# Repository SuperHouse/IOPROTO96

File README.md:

I/O Breakout To Prototyping Area (96 Point)
===========================================
Copyright 2017 SuperHouse Pty Ltd  
SuperHouse site:  www.superhouse.tv  

Breaks out a 2x6 pin header to a 96-point prototyping area.

Features:

 * 8 data lines
 * GND, VIN, IOREF, and RESET passed through
 * 8x12 grid prototyping area

More information is available at:

  http://www.superhouse.tv/ioproto96

INSTALLATION
------------
The design is saved as an EAGLE project. EAGLE PCB design software is
available from www.cadsoftusa.com free for non-commercial use. To use
this project download it and place the directory containing these files
into the "eagle" directory on your computer. Then open EAGLE and
navigate to the project.

DISTRIBUTION
------------
The specific terms of distribution of this project are governed by the
license referenced below.

LICENSE
-------
Licensed under the TAPR Open Hardware License (www.tapr.org/OHL).
The "license" folder within this repository also contains a copy of
this license in plain text format.

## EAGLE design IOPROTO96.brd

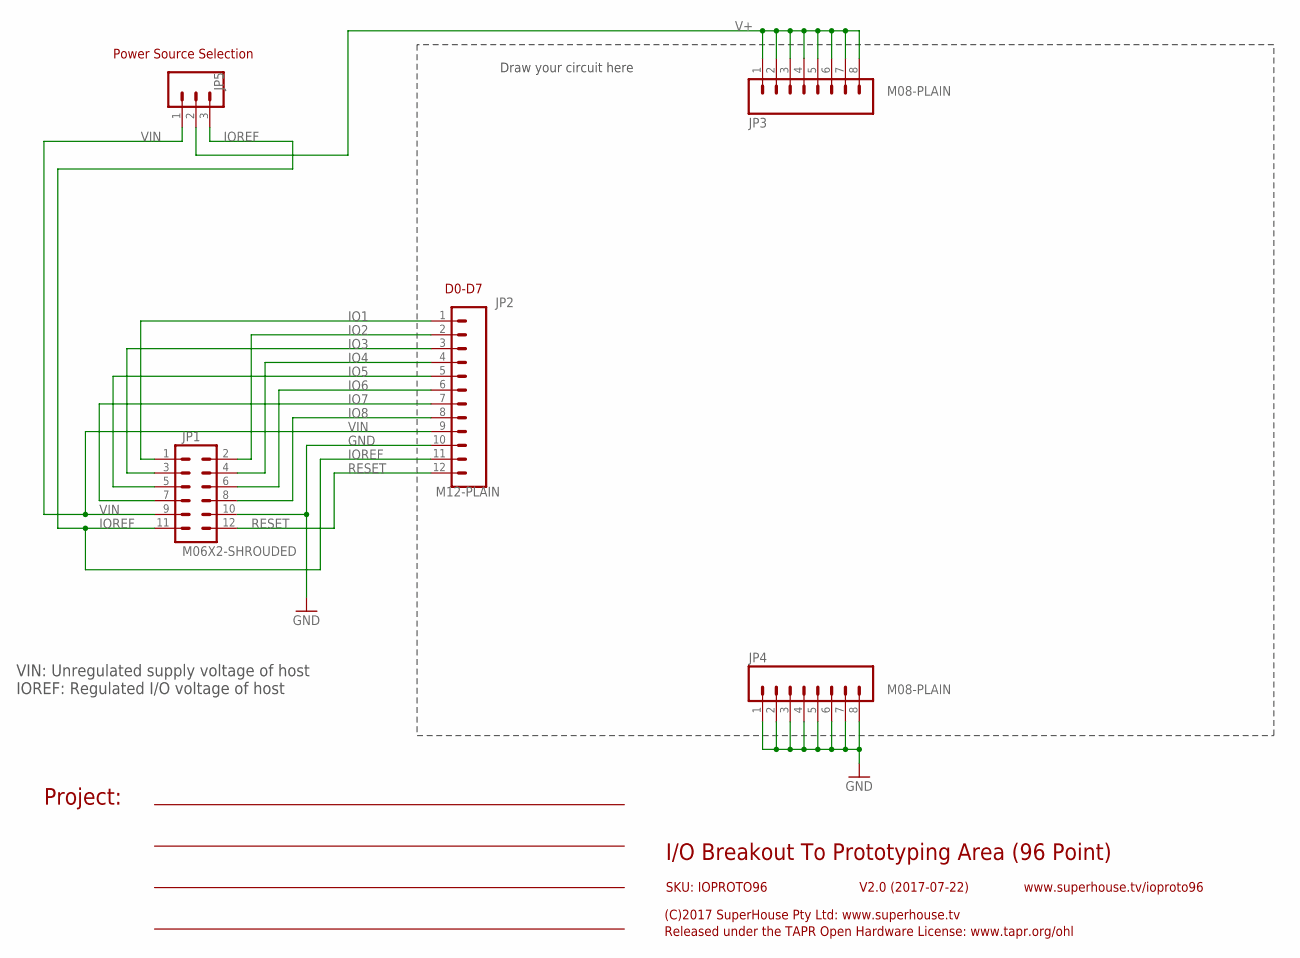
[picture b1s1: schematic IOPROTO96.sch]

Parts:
JP1: M06X2-SHROUDED; 2X6-SHROUDED
JP2: M12-PLAIN; 1X12
JP3, JP4: M08-PLAIN; 1X08
JP5: M03-PIN; 1X03-P

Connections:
GND: JP1.10, JP2.10, JP4.1, JP4.2, JP4.3, JP4.4, JP4.5, JP4.6, JP4.7, JP4.8
IO1: JP1.1, JP2.1
IO2: JP1.2, JP2.2
IO3: JP1.3, JP2.3
IO4: JP1.4, JP2.4
IO5: JP1.5, JP2.5
IO6: JP1.6, JP2.6
IO7: JP1.7, JP2.7
IO8: JP1.8, JP2.8
IOREF: JP1.11, JP2.11, JP5.3
RESET: JP1.12, JP2.12
V+: JP3.1, JP3.2, JP3.3, JP3.4, JP3.5, JP3.6, JP3.7, JP3.8, JP5.2
VIN: JP1.9, JP2.9, JP5.1

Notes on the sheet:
D0-D7
I/O Breakout To Prototyping Area (96 Point)
V2.0 (2017-07-22)
SKU: IOPROTO96
(C)2017 SuperHouse Pty Ltd: www.superhouse.tv
Released under the TAPR Open Hardware License: www.tapr.org/ohl
www.superhouse.tv/ioproto96
Draw your circuit here
Project:
VIN: Unregulated supply voltage of host IOREF: Regulated I/O voltage of host
Power Source Selection

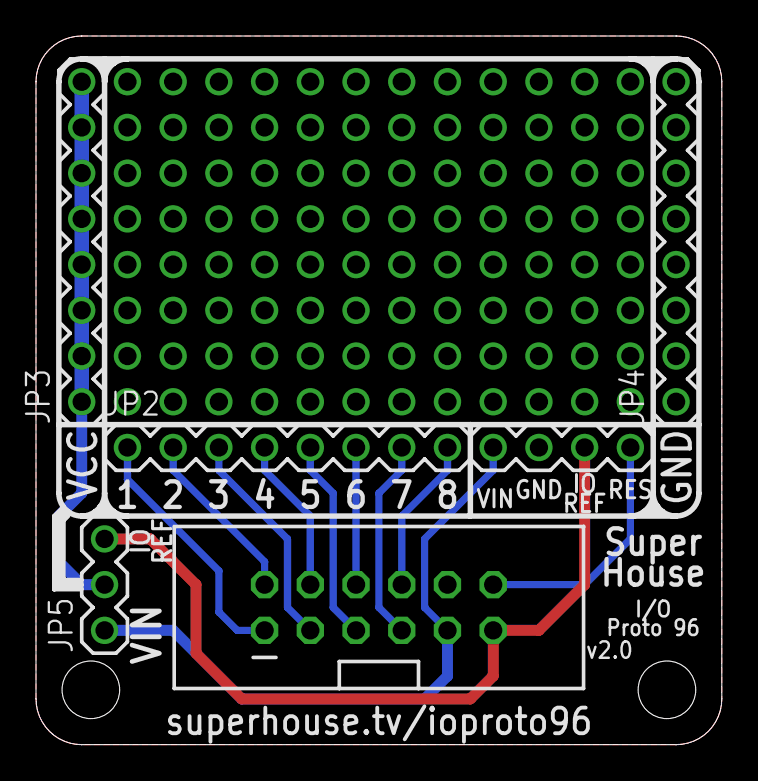
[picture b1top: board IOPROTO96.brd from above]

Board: 2 copper layers, 38.1 x 39.4 mm, 5 parts (0 on the bottom side), 13 nets.

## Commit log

2017-07-22 Initial project import
2017-07-24 Updated silkscreen for v2.0 release
2017-07-24 Updated README for v2.0 release
2017-07-25 Final routing and DRC for release v2.0
2019-09-14 Part replacement using SuperHouse libraries
